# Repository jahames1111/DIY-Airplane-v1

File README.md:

# DIY-Airplane-v1

I have made many attempts to create some type of flying thing before, and they always failed because of a low budget. This is my first try that actually holds some promise. I will be creating both a remote and a receiver from scratch — the remote will use joysticks and XIAO boards I already have, and the FC board will be JLCPCB+LCSC. 

## Overview
This project contains 2 parts:
1. A flight controller board running brushless motors. It is built off of a XIAO ESP32C3 and has 2 breakouts that are optional for a NEO 6M GPS module and an MPU9250. Runs on one 450mah 1S battery and has 2 100k resistors for a voltage divider for reading remaining battery levels.
   
3. A remote using 2 analog joysticks with push buttons, another XIAO C3, and a 240x240 circular screen for showing battery levels for both. The remote runs on a 5v battery pack.

### Project Materials

| Component Name | Description | Source Link |
| :--- | :--- | :--- |
| **XIAO ESP32-C3** | Microcontroller wireless link | [Datasheet](https://wiki.seeedstudio.com/XIAO_ESP32C3_Getting_Started/) |
| **Analog Joystick** | Manual thumbstick control | [Reference](https://components101.com/modules/joystick-module) |
| **GC9A01 Display** | Circular screen telemetry | [Driver](https://www.waveshare.com/wiki/1.28inch_LCD_Module) |
| **NEO-6M GPS** | Satellite navigation tracking | [Reference](https://components101.com/modules/neo-6mv2-gps-module) |
| **MPU9250 IMU** | Motion tracking gyro | [Specification](https://product.tdk.com/en/search/sensor/mortion-inertial/imu/info?part_no=MPU-9250) |
| **Brushed Motors** | Coreless propulsion drive | [Reference](https://www.adafruit.com/product/711) |
| **Foam Board** | Lightweight airframe structure | [Guide](https://www.flitetest.com/articles/ft-scratchbuild-build-videos) |
| **IRLB8721PBF-JSM** | Motor switching gate | [LCSC](https://www.lcsc.com/product-detail/MOSFETs_JSMSEMI-IRLB8721PBF-JSM_C52948633.html) |
| **1N4001 Diode** | Circuit flyback protection | [LCSC](https://www.lcsc.com/search?q=1N4001) |
| **10kΩ Resistor** | Gate pull down | [LCSC](https://www.lcsc.com/product-detail/Through-Hole-Resistors_UNI-ROYAL-MFR0W4F1002A50_C57436.html) |
| **100kΩ Resistor** | Telemetry voltage divider | [LCSC](https://www.lcsc.com/product-detail/Through-Hole-Resistors_YAGEO-MFR-25FRF52-100K_C1740093.html) |

## Assembly

The main body of the plane will be constructed of foam that I will buy at Dollar Tree, and I will assemble it according to [this guide](https://canva.link/13dvw4ls8qo39oa) I downloaded.
Since it has 2 motors, I can have one side speed up to bank the other way, or have both speed up/slow down to adjust pitch.

I also designed a 3d printed case for the transmitter, so here is the Onshape link:
https://cad.onshape.com/documents/e551e0e861c010d2a69231d2/w/2bc16dd78661a5521259ed7d/e/f502e56e68dee0d14d4a1407?renderMode=0&uiState=6ae8e8fff03f46e928020b88

## Specs
- Flight controller board: ~3 inches by ~2/3 inches
- Remote: ~180mm by ~80mm
- Airplane: 12"x18"
- 1S battery system

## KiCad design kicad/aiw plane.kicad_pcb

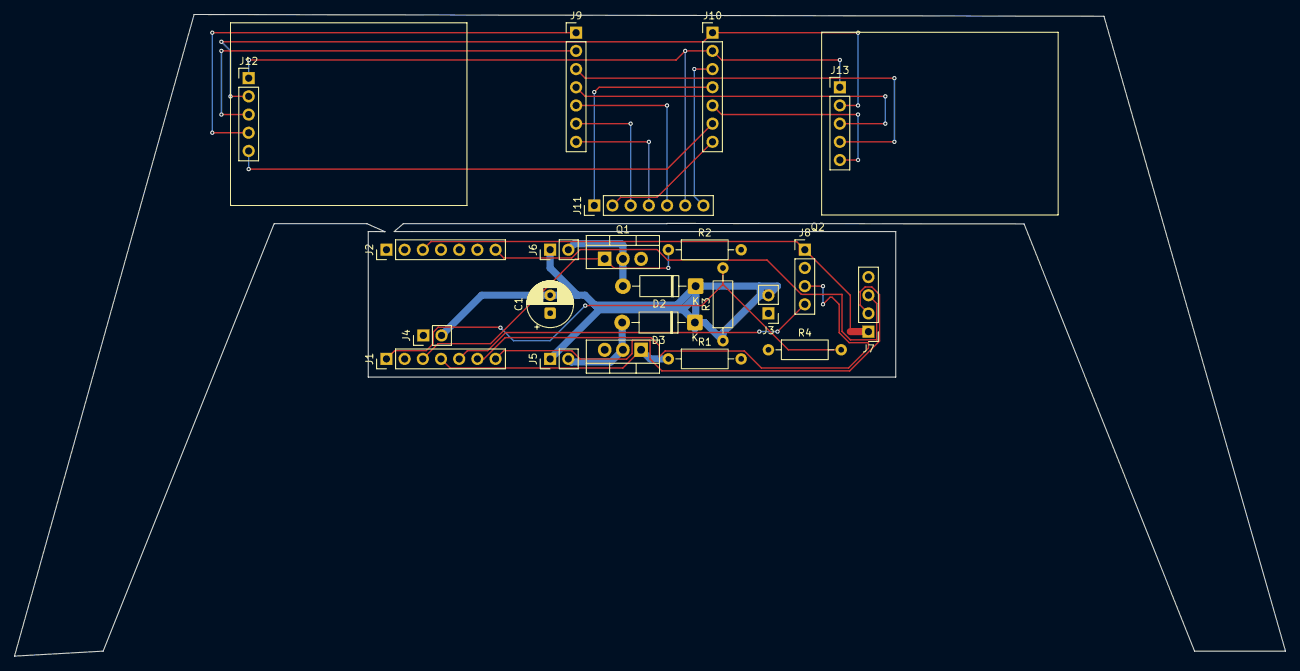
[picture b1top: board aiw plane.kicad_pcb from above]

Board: 2 copper layers, 177.5 x 89.6 mm, 22 parts (0 on the bottom side), 26 nets.

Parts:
C1: 470uF; CP_Radial_D6.3mm_P2.50mm
D2, D3: 1N4001; D_DO-41_SOD81_P10.16mm_Horizontal
J1, J2, J9, J10, J11: Conn_01x07_Pin; PinHeader_1x07_P2.54mm_Vertical
J3, J4, J5, J6: Conn_01x02_Pin; PinHeader_1x02_P2.54mm_Vertical
J7, J8: Conn_01x04_Pin; PinHeader_1x04_P2.54mm_Vertical
J12, J13: Conn_01x05_Pin; PinHeader_1x05_P2.54mm_Vertical
Q1, Q2: IRLB8721PBF; TO-220-3_Vertical
R1, R2: 10k; R_Axial_DIN0207_L6.3mm_D2.5mm_P10.16mm_Horizontal
R3, R4: 100k; R_Axial_DIN0207_L6.3mm_D2.5mm_P10.16mm_Horizontal

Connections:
/3: J2.3, J7.1, J8.1
/3v3: J10.3, J11.7
/5: J10.1, J12.2, J13.2
/b: C1.2, D2.1 (K), D3.1 (K), J3.2, J4.2, J5.1, J6.1, R3.1
/cs: J10.7, J11.2
/d6: J1.7, J7.2
/d7: J2.7, J7.3
/dc: J9.6, J11.3
/g: C1.1, J2.2, J3.1, J4.1, J7.4, J8.2, Q1.3 (S), Q2.3 (S), R1.2, R2.2, R4.1
/gnd: J10.2, J11.6, J12.1, J13.1
/m1: J1.3, Q1.1 (G), R2.1
/m2: J1.4, Q2.1 (G), R1.1
/rst: J10.4, J11.1
/scl: J1.6, J8.3
/scls: J9.5, J11.5
/sda: J1.5, J8.4
/sdas: J9.7, J11.4
/sw1: J10.6, J12.5
/sw2: J10.5, J13.5
/x1: J9.2, J12.3
/x2: J9.4, J13.3
/y1: J9.1, J12.4
/y2: J9.3, J13.4
unnamed: D2.2 (A), J6.2, Q1.2 (D)
unnamed: D3.2 (A), J5.2, Q2.2 (D)
unnamed: J1.1, R3.2, R4.2

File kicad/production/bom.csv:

Designator,Footprint,Quantity,Value,LCSC Part #
C1,CP_Radial_D6.3mm_P2.50mm,1,470uF,
"D2, D3",D_DO-41_SOD81_P10.16mm_Horizontal,2,1N4001,
"J1, J10, J11, J2, J9",PinHeader_1x07_P2.54mm_Vertical,5,Conn_01x07_Pin,
"J12, J13",PinHeader_1x05_P2.54mm_Vertical,2,Conn_01x05_Pin,
"J3, J4, J5, J6",PinHeader_1x02_P2.54mm_Vertical,4,Conn_01x02_Pin,
"J7, J8",PinHeader_1x04_P2.54mm_Vertical,2,Conn_01x04_Pin,
"Q1, Q2",TO-220-3_Vertical,2,IRLB8721PBF,
"R1, R2",R_Axial_DIN0207_L6.3mm_D2.5mm_P10.16mm_Horizontal,2,10k,
"R3, R4",R_Axial_DIN0207_L6.3mm_D2.5mm_P10.16mm_Horizontal,2,100k,
